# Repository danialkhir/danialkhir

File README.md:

- 👋 Hi, I’m @danialkhir

For Electronics Design Refer to :
/Automatic Continuity Tester
/Fan Tester

For Firmware Design Refer to:
/Automatic Continuity Tester
/Fan Tester
/MPU6050

For 3D Design Refer to:
/Automatic Continuity Tester
/Fan Tester
/MPU6050

For Software Design Refer to:
/DFM Report Generator
/SCPI Project 

Thanks Look Forward for our next ventures

<!---
danialkhir/danialkhir is a ✨ special ✨ repository because its `README.md` (this file) appears on your GitHub profile.
You can click the Preview link to take a look at your changes.
--->

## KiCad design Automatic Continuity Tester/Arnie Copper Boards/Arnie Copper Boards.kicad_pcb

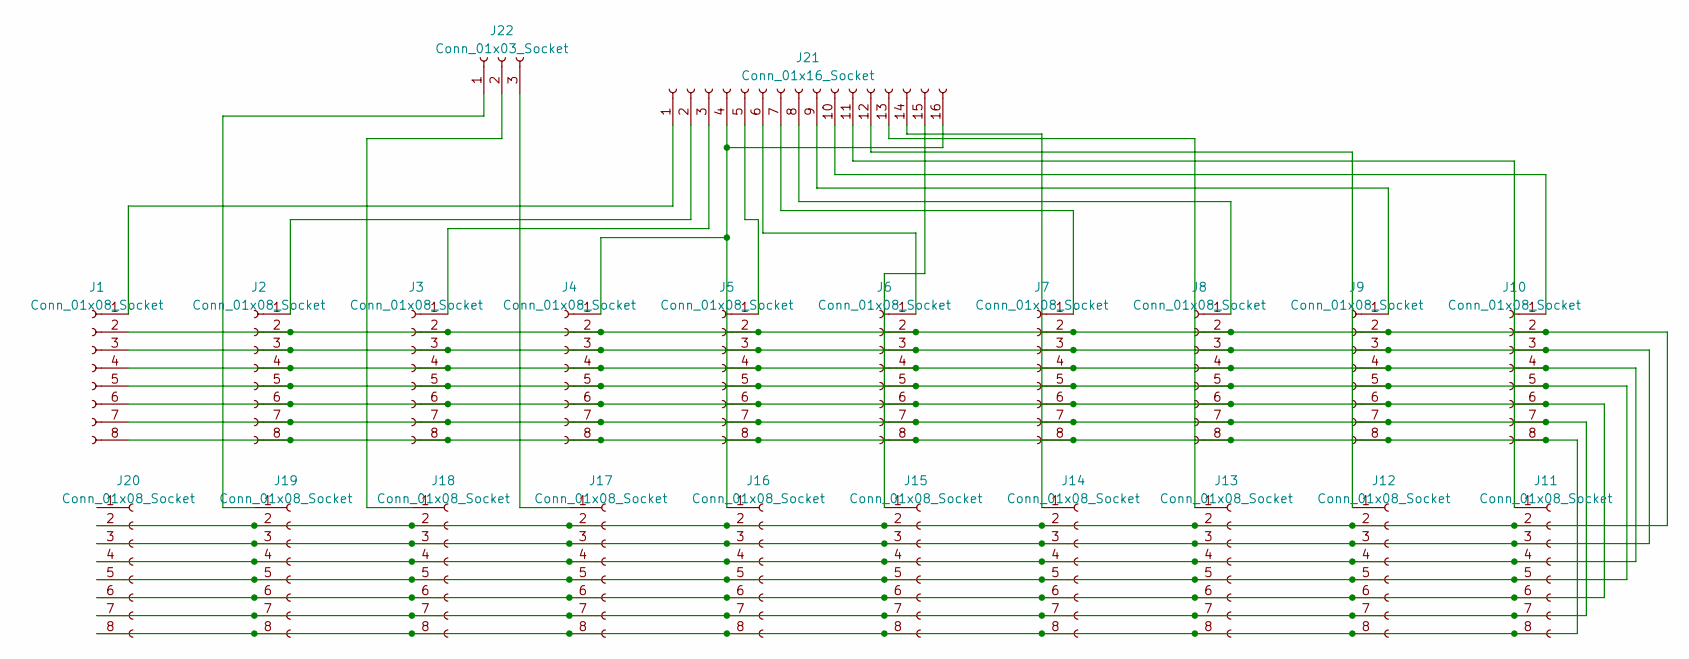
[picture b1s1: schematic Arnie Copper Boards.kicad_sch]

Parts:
J1, J2, J3, J4, J5, J6, J7, J8, J9, J10, J11, J12, J13, J14, J15, J16, J17, J18, J19, J20: Conn_01x08_Socket; JST_EH_B8B-EH-A_1x08_P2.50mm_Vertical
J21: Conn_01x16_Socket; PinHeader_1x16_P2.54mm_Horizontal
J22: Conn_01x03_Socket; PinHeader_1x03_P2.54mm_Vertical_SMD_Pin1Right

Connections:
unnamed: J1.1, J21.1
unnamed: J1.2, J2.2, J3.2, J4.2, J5.2, J6.2, J7.2, J8.2, J9.2, J10.2, J11.2, J12.2, J13.2, J14.2, J15.2, J16.2, J17.2, J18.2, J19.2, J20.2
unnamed: J1.3, J2.3, J3.3, J4.3, J5.3, J6.3, J7.3, J8.3, J9.3, J10.3, J11.3, J12.3, J13.3, J14.3, J15.3, J16.3, J17.3, J18.3, J19.3, J20.3
unnamed: J1.4, J2.4, J3.4, J4.4, J5.4, J6.4, J7.4, J8.4, J9.4, J10.4, J11.4, J12.4, J13.4, J14.4, J15.4, J16.4, J17.4, J18.4, J19.4, J20.4
unnamed: J1.5, J2.5, J3.5, J4.5, J5.5, J6.5, J7.5, J8.5, J9.5, J10.5, J11.5, J12.5, J13.5, J14.5, J15.5, J16.5, J17.5, J18.5, J19.5, J20.5
unnamed: J1.6, J2.6, J3.6, J4.6, J5.6, J6.6, J7.6, J8.6, J9.6, J10.6, J11.6, J12.6, J13.6, J14.6, J15.6, J16.6, J17.6, J18.6, J19.6, J20.6
unnamed: J1.7, J2.7, J3.7, J4.7, J5.7, J6.7, J7.7, J8.7, J9.7, J10.7, J11.7, J12.7, J13.7, J14.7, J15.7, J16.7, J17.7, J18.7, J19.7, J20.7
unnamed: J1.8, J2.8, J3.8, J4.8, J5.8, J6.8, J7.8, J8.8, J9.8, J10.8, J11.8, J12.8, J13.8, J14.8, J15.8, J16.8, J17.8, J18.8, J19.8, J20.8
unnamed: J2.1, J21.2
unnamed: J10.1, J21.10
unnamed: J11.1, J21.11
unnamed: J12.1, J21.12
unnamed: J13.1, J21.13
unnamed: J14.1, J21.14
unnamed: J15.1, J21.15
unnamed: J4.1, J16.1, J21.4, J21.16
unnamed: J17.1, J22.3
unnamed: J18.1, J22.2
unnamed: J19.1, J22.1
unnamed: J3.1, J21.3
unnamed: J5.1, J21.5
unnamed: J6.1, J21.6
unnamed: J7.1, J21.7
unnamed: J8.1, J21.8
unnamed: J9.1, J21.9

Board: 2 copper layers, 22 parts (0 on the bottom side), 25 nets, no tracks yet.

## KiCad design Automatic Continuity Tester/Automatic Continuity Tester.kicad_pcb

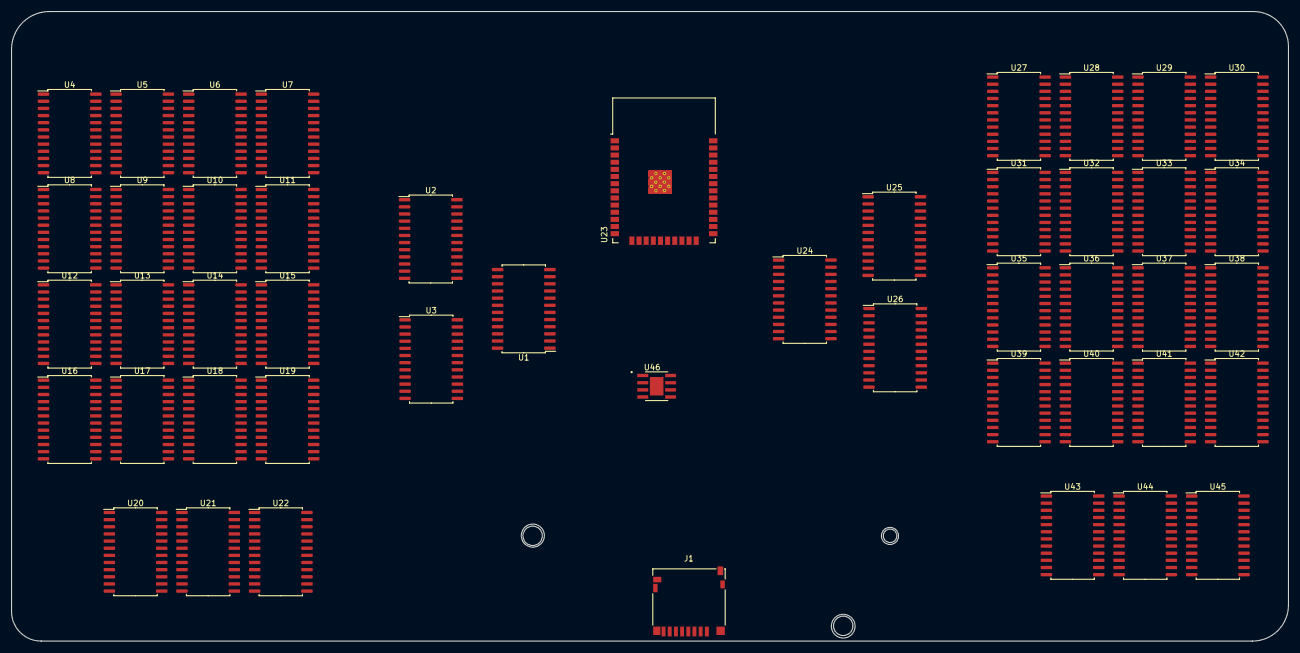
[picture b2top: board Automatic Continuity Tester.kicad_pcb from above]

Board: 2 copper layers, 227.0 x 111.9 mm, 48 parts (1 on the bottom side), 48 nets, no tracks yet.

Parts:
BT1: Battery_Cell; BatteryHolder_Keystone_1042_1x18650
J1: Micro_SD_Card; microSD_HC_Hirose_DM3D-SF
U1, U2, U3, U4, U5, U6, U7, U8, U9, U10, U11, U12, U13, U14, U15, U16, U17, U18, U19, U20, U21, U22, U24, U25, U26, U27, U28, U29, U30, U31, U32, U33, U34, U35, U36, U37, U38, U39, U40, U41, U42, U43, U44, U45: CD74HC4067M; SOIC-24W_7.5x15.4mm_P1.27mm
U23: ESP32-WROOM-32
U46: TP4056; SOP127P600X175-9N

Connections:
01: U2.9 (I0), U4.1 (COM), U25.9 (I0), U30.1 (COM)
02: U2.8 (I1), U5.1 (COM), U25.8 (I1), U27.1 (COM)
03: U2.7 (I2), U6.1 (COM), U25.7 (I2), U28.1 (COM)
04: U2.6 (I3), U10.1 (COM), U25.6 (I3), U29.1 (COM)
05: U2.5 (I4), U11.1 (COM), U25.5 (I4), U34.1 (COM)
06: U2.4 (I5), U9.1 (COM), U25.4 (I5), U33.1 (COM)
07: U2.3 (I6), U7.1 (COM), U25.3 (I6), U32.1 (COM)
08: U2.2 (I7), U8.1 (COM), U25.2 (I7), U31.1 (COM)
09: U2.23 (I8), U15.1 (COM), U25.23 (I8), U38.1 (COM)
010: U2.22 (I9), U14.1 (COM), U25.22 (I9), U37.1 (COM)
11: U3.9 (I0), U20.1 (COM), U26.9 (I0), U43.1 (COM)
011: U2.21 (I10), U12.1 (COM), U25.21 (I10), U35.1 (COM)
12: U3.8 (I1), U22.1 (COM), U26.8 (I1), U45.1 (COM)
012: U2.20 (I11), U13.1 (COM), U25.20 (I11), U36.1 (COM)
013: U2.19 (I12), U19.1 (COM), U25.19 (I12), U42.1 (COM)
13: U3.7 (I2), U21.1 (COM), U26.7 (I2), U44.1 (COM)
014: U2.18 (I13), U18.1 (COM), U25.18 (I13), U41.1 (COM)
015: U2.17 (I14), U16.1 (COM), U25.17 (I14), U39.1 (COM)
016: U2.16 (I15), U17.1 (COM), U25.16 (I15), U40.1 (COM)
+3.3V: U1.24 (VCC), U2.24 (VCC), U3.24 (VCC), U4.24 (VCC), U5.24 (VCC), U6.24 (VCC), U7.24 (VCC), U8.24 (VCC), U9.24 (VCC), U10.24 (VCC), U11.24 (VCC), U13.24 (VCC), U14.24 (VCC), U15.24 (VCC), U16.24 (VCC), U17.24 (VCC), U18.24 (VCC), U19.24 (VCC), U20.24 (VCC), U21.24 (VCC), U22.24 (VCC), U24.24 (VCC), U25.24 (VCC), U26.24 (VCC), U27.24 (VCC), U28.24 (VCC), U29.24 (VCC), U30.24 (VCC), U31.24 (VCC), U32.24 (VCC), U33.24 (VCC), U34.24 (VCC), U35.24 (VCC), U36.24 (VCC), U37.24 (VCC), U38.24 (VCC), U39.24 (VCC), U40.24 (VCC), U41.24 (VCC), U42.24 (VCC), U43.24 (VCC), U44.24 (VCC), U45.24 (VCC)
+5V: U23.2 (VDD), U46.4 (VCC)
B0: U1.10 (S0), U23.25 (IO0)
B1: U2.10 (S0), U3.10 (S0), U23.35 (TXD0/IO1)
B2: U2.11 (S1), U3.11 (S1), U23.24 (IO2)
B3: U2.14 (S2), U3.14 (S2), U23.34 (RXD0/IO3)
B4: U2.13 (S3), U3.13 (S3), U23.26 (IO4)
B5: U4.10 (S0), U5.10 (S0), U6.10 (S0), U7.10 (S0), U8.10 (S0), U9.10 (S0), U10.10 (S0), U11.10 (S0), U12.10 (S0), U13.10 (S0), U14.10 (S0), U15.10 (S0), U16.10 (S0), U17.10 (S0), U18.10 (S0), U19.10 (S0), U20.10 (S0), U21.10 (S0), U22.10 (S0), U23.29 (IO5)
B6: U4.11 (S1), U5.11 (S1), U6.11 (S1), U7.11 (S1), U8.11 (S1), U9.11 (S1), U10.11 (S1), U11.11 (S1), U12.11 (S1), U13.11 (S1), U14.11 (S1), U15.11 (S1), U16.11 (S1), U17.11 (S1), U18.11 (S1), U19.11 (S1), U20.11 (S1), U21.11 (S1), U22.11 (S1), U23.14 (IO12)
B7: U4.14 (S2), U5.14 (S2), U6.14 (S2), U7.14 (S2), U8.14 (S2), U9.14 (S2), U10.14 (S2), U11.14 (S2), U12.14 (S2), U13.14 (S2), U14.14 (S2), U15.14 (S2), U16.14 (S2), U17.14 (S2), U18.14 (S2), U19.14 (S2), U20.14 (S2), U21.14 (S2), U22.14 (S2), U23.16 (IO13)
B8: U4.13 (S3), U5.13 (S3), U6.13 (S3), U7.13 (S3), U8.13 (S3), U9.13 (S3), U10.13 (S3), U11.13 (S3), U12.13 (S3), U13.13 (S3), U14.13 (S3), U15.13 (S3), U16.13 (S3), U17.13 (S3), U18.13 (S3), U19.13 (S3), U20.13 (S3), U21.13 (S3), U22.13 (S3), U23.13 (IO14)
D0: U23.23 (IO15), U24.10 (S0)
D1: U23.27 (IO16), U25.10 (S0), U26.10 (S0)
D2: U23.28 (IO17), U25.11 (S1), U26.11 (S1)
D3: U23.30 (IO18), U25.14 (S2), U26.14 (S2)
D4: U23.31 (IO19), U25.13 (S3), U26.13 (S3)
D5: U23.33 (IO21), U27.10 (S0), U28.10 (S0), U29.10 (S0), U30.10 (S0), U31.10 (S0), U32.10 (S0), U33.10 (S0), U34.10 (S0), U35.10 (S0), U36.10 (S0), U37.10 (S0), U38.10 (S0), U39.10 (S0), U40.10 (S0), U41.10 (S0), U42.10 (S0), U43.10 (S0), U44.10 (S0), U45.10 (S0)
D6: U23.36 (IO22), U27.11 (S1), U28.11 (S1), U29.11 (S1), U30.11 (S1), U31.11 (S1), U32.11 (S1), U33.11 (S1), U34.11 (S1), U35.11 (S1), U36.11 (S1), U37.11 (S1), U38.11 (S1), U39.11 (S1), U40.11 (S1), U41.11 (S1), U42.11 (S1), U43.11 (S1), U44.11 (S1), U45.11 (S1)
D7: U23.37 (IO23), U27.14 (S2), U28.14 (S2), U29.14 (S2), U30.14 (S2), U31.14 (S2), U32.14 (S2), U33.14 (S2), U34.14 (S2), U35.14 (S2), U36.14 (S2), U37.14 (S2), U38.14 (S2), U39.14 (S2), U40.14 (S2), U41.14 (S2), U42.14 (S2), U43.14 (S2), U44.14 (S2), U45.14 (S2)
D8: U23.12 (IO27), U27.13 (S3), U28.13 (S3), U29.13 (S3), U30.13 (S3), U31.13 (S3), U32.13 (S3), U33.13 (S3), U34.13 (S3), U35.13 (S3), U36.13 (S3), U37.13 (S3), U38.13 (S3), U39.13 (S3), U40.13 (S3), U41.13 (S3), U42.13 (S3), U43.13 (S3), U44.13 (S3), U45.13 (S3)
GND: BT1.2 (-), U1.12 (GND), U2.12 (GND), U3.12 (GND), U4.12 (GND), U4.15 (~E), U5.12 (GND), U5.15 (~E), U6.12 (GND), U6.15 (~E), U7.12 (GND), U8.12 (GND), U8.15 (~E), U9.12 (GND), U10.12 (GND), U10.15 (~E), U11.12 (GND), U12.12 (GND), U12.15 (~E), U13.12 (GND), U14.12 (GND), U15.12 (GND), U16.12 (GND), U17.12 (GND), U18.12 (GND), U19.12 (GND), U20.12 (GND), U21.12 (GND), U22.12 (GND), U23.1 (GND), U23.15 (GND), U23.38 (GND), U23.39 (GND), U24.12 (GND), U25.12 (GND), U26.12 (GND), U27.12 (GND), U28.12 (GND), U29.12 (GND), U30.12 (GND), U31.12 (GND), U32.12 (GND), U33.12 (GND), U34.12 (GND), U35.12 (GND), U36.12 (GND), U37.12 (GND), U38.12 (GND), U39.12 (GND), U40.12 (GND), U41.12 (GND), U42.12 (GND), U43.12 (GND), U44.12 (GND), U45.12 (GND), U46.3 (GND)
unnamed: BT1.1 (+), J1.5 (CLK), J1.6 (VSS), U23.20 (SCK/CLK), U46.5 (BAT)
unnamed: J1.3 (CMD), U23.19 (SCS/CMD)
unnamed: U1.9 (I0), U2.1 (COM)
unnamed: U1.8 (I1), U3.1 (COM)
unnamed: U24.9 (I0), U25.1 (COM)
unnamed: U24.8 (I1), U26.1 (COM)
P25: U1.1 (COM), U23.10 (IO25)
P26: U23.11 (IO26), U24.1 (COM)

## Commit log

2024-03-08 Who I am.md
2024-03-08 Create Continuity Tester Master
    Master Code for Continuity Tester Project
2024-03-08 Create Continuity Tester
